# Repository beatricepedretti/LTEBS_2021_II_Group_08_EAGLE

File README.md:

# LTEBS_2021_II_Group_08_EAGLE

This repository contains the first project for the Electronic Technologies and Biosensors Laboratory course, part of the Biomedical Engineering MSc at Politecnico di Milano.
In this project we designed a schematic, a PCB and two custom components using Autodesk EAGLE. The aim of the work was to design a PCB embedding the PSoC 5LP micro-controller in order to evaluate its performance.

# PCB relevant info

- The PCB manufacturer is MDSrl and therefore we followed the rules explained on their website for PCB design (https://www.mdpcb.com/mddesignrules.html).
the 10mil minimum track width requested in the assignment specifications caused clearance errors at the pins of the MUX, therefore we routed this component using 8mil wires while still using 10mils wires everywhere else. This choice satisfies the manufacturer requirements which report 6mils as the minimum width for traces.
- We positioned the light sensor as far away as possible from the LED in order to avoid luminous interference given by the LED. We also tried to position the light sensor as isolated as possible from "tall" components in order to avoid shadows that could interfere with the sensor's measurements.
- We positioned the temperature sensor as far away as possible from the power supply in order to avoid interference given by possible heating of the power supply.
- For the copper pour we used isolation 8 that is the minimum allowed by the manufacturer
- We put jumpers on side of the board

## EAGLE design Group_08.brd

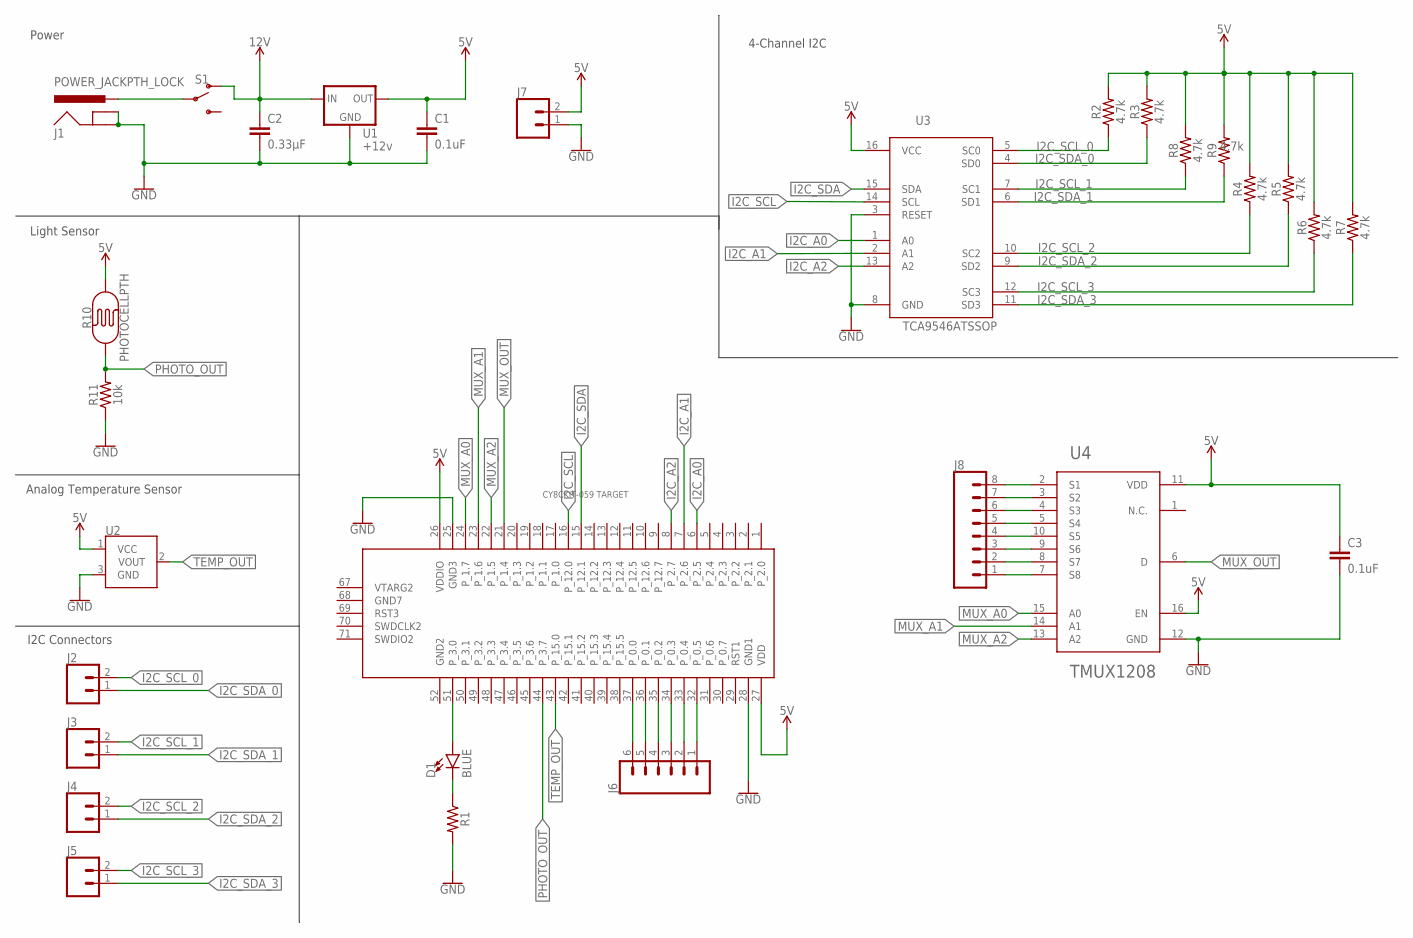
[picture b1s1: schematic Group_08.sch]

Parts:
C1, C3: 0.1uF; CAP-PTH-SMALL-KIT
C2: 0.33µF; 0805
CY8CKIT059-TARGET: CY8CKIT-059_TARGET
D1: BLUE; LED-1206
J1: POWER_JACKPTH_LOCK; POWER_JACK_PTH_LOCK
J2, J3, J4, J5, J7: CONN_02; 1X02
J6: CONN_06LOCK; 1X06_LOCK
J8: CONN_08LOCK; 1X08_LOCK
R1: RESISTORAXIAL-0.3; AXIAL-0.3
R2, R3, R4, R5, R6, R7, R8, R9: 4.7k; 0603
R10: PHOTOCELLPTH; PHOTOCELL
R11: 10k; 0603
S1: SWITCH-SPDT-PTH-11.6X4.0MM; SWITCH_SPDT_PTH_11.6X4.0MM
U1: +12v; TO-252
U2: TMP36GT9; TO-92
U3: TCA9546ATSSOP; TSSOP16
U4: TMUX1208; QFN16

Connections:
5V: C1.1, C3.1, CY8CKIT059-TARGET.26 (VDDIO), CY8CKIT059-TARGET.27 (VDD), J7.2, R2.2, R3.2, R4.2, R5.2, R6.2, R7.2, R8.2, R9.2, R10.2, U1.2 (OUT), U2.1 (VCC), U3.16 (VCC), U4.11 (VDD), U4.16 (EN)
12V: C2.1, S1.1 (O), U1.1 (IN)
GND: C1.2, C2.2, C3.2, CY8CKIT059-TARGET.25 (GND3), CY8CKIT059-TARGET.28 (GND1), J1.GND, J1.GNDBREAK, J7.1, R1.P$2 (2), R11.1, U1.3 (GND), U2.3 (GND), U3.3 (RESET), U3.8 (GND), U4.12 (GND)
I2C_A0: CY8CKIT059-TARGET.6 (P_2.5), U3.1 (A0)
I2C_A1: CY8CKIT059-TARGET.7 (P_2.6), U3.2 (A1)
I2C_A2: CY8CKIT059-TARGET.8 (P_2.7), U3.13 (A2)
I2C_SCL: CY8CKIT059-TARGET.16 (P_12.0), U3.14 (SCL)
I2C_SCL_0: J2.2, R2.1, U3.5 (SC0)
I2C_SCL_1: J3.2, R8.1, U3.7 (SC1)
I2C_SCL_2: J4.2, R4.1, U3.10 (SC2)
I2C_SCL_3: J5.2, R6.1, U3.12 (SC3)
I2C_SDA: CY8CKIT059-TARGET.15 (P_12.1), U3.15 (SDA)
I2C_SDA_0: J2.1, R3.1, U3.4 (SD0)
I2C_SDA_1: J3.1, R9.1, U3.6 (SD1)
I2C_SDA_2: J4.1, R5.1, U3.9 (SD2)
I2C_SDA_3: J5.1, R7.1, U3.11 (SD3)
MUX_A0: CY8CKIT059-TARGET.24 (P_1.7), U4.15 (A0)
MUX_A1: CY8CKIT059-TARGET.23 (P_1.6), U4.14 (A1)
MUX_A2: CY8CKIT059-TARGET.22 (P_1.5), U4.13 (A2)
MUX_OUT: CY8CKIT059-TARGET.21 (P_1.4), U4.6 (D)
unnamed: J1.PWR, S1.2
unnamed: J8.1, U4.7 (S8)
unnamed: J8.2, U4.8 (S7)
unnamed: J8.3, U4.9 (S6)
unnamed: J8.4, U4.10 (S5)
unnamed: J8.5, U4.5 (S4)
unnamed: J8.6, U4.4 (S3)
unnamed: J8.7, U4.3 (S2)
unnamed: J8.8, U4.2 (S1)
unnamed: CY8CKIT059-TARGET.37 (P_0.0), J6.6
unnamed: CY8CKIT059-TARGET.32 (P_0.5), J6.1
unnamed: CY8CKIT059-TARGET.33 (P_0.4), J6.2
unnamed: CY8CKIT059-TARGET.34 (P_0.3), J6.3
unnamed: CY8CKIT059-TARGET.35 (P_0.2), J6.4
unnamed: CY8CKIT059-TARGET.36 (P_0.1), J6.5
unnamed: D1.C, R1.P$1 (1)
unnamed: CY8CKIT059-TARGET.51 (P_3.0), D1.A
PHOTO_OUT: CY8CKIT059-TARGET.44 (P_3.7), R10.1, R11.2
TEMP_OUT: CY8CKIT059-TARGET.43 (P_15.0), U2.2 (VOUT)

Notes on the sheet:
Light Sensor
Analog Temperature Sensor
Power
4-Channel I2C
I2C Connectors

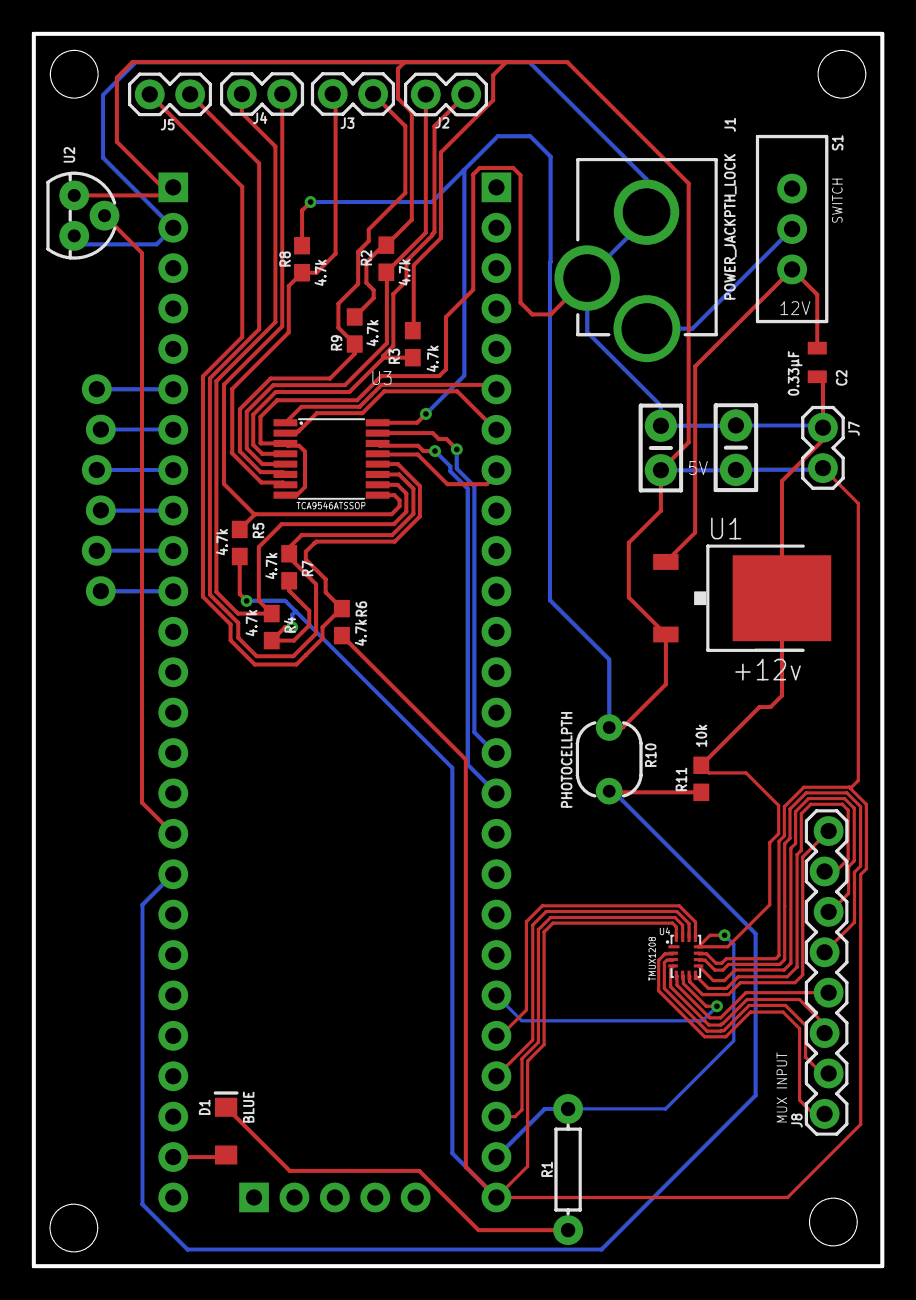
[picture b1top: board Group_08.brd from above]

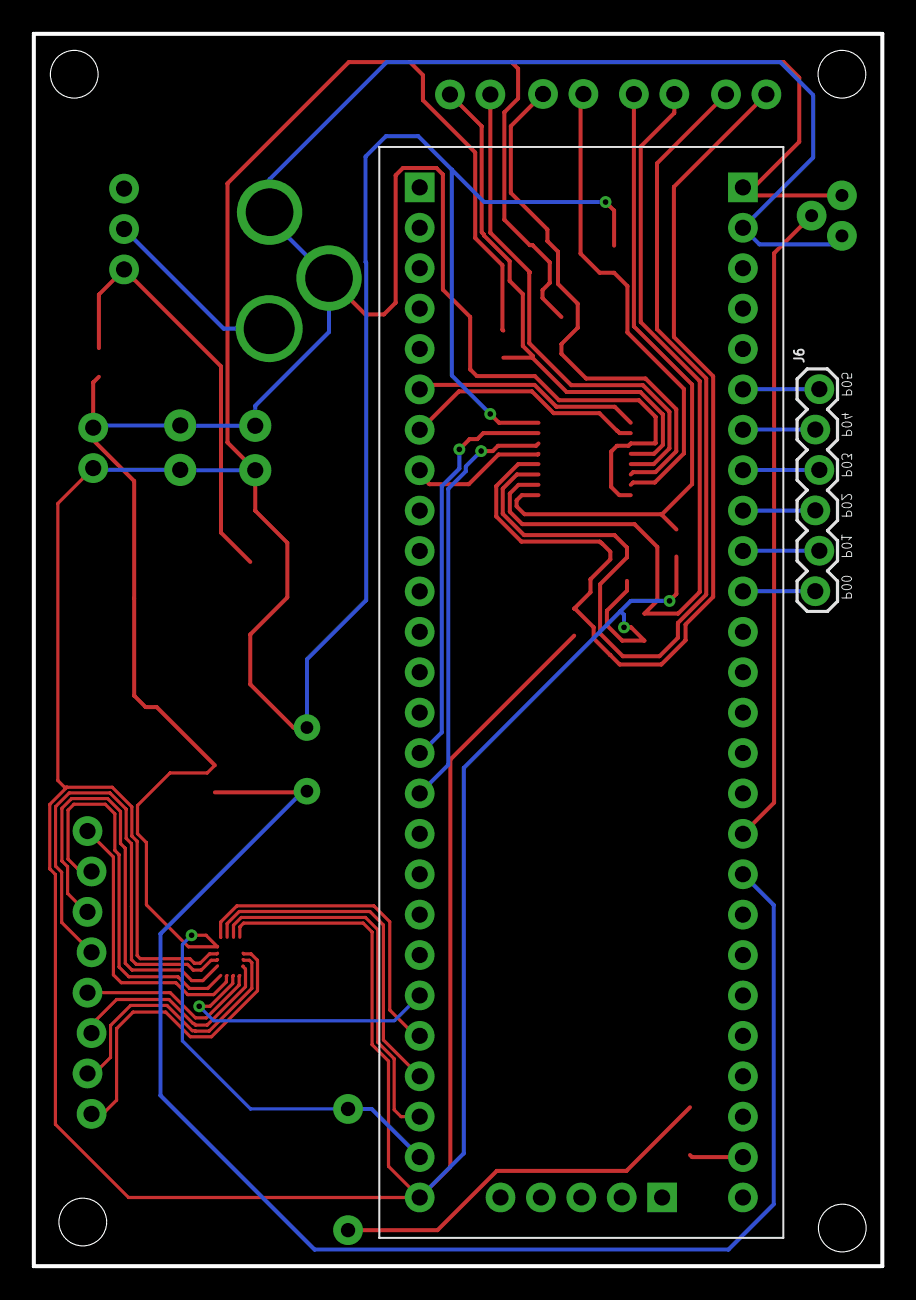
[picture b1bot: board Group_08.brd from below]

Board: 2 copper layers, 53.3 x 77.5 mm, 29 parts (2 on the bottom side), 39 nets.

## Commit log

2021-03-19 Removed .pdf files
2021-03-19 Added TMUX1208 device to general library ('Group_08_Library.lbr') for the moment. Saved the device in an additional library ('TMUX1208.lbr') for safety.
2021-03-19 Modified TMUX1208 symbol in both libraries
2021-03-19 Modified symbol to match reference schematics
2021-03-20 = Added TCA9546A
2021-03-20 Deleted backup file
2021-03-20 Adjusted TMUX1208 footprint
2021-03-22 Modified description headline of device
2021-03-22 First schematic prototype. Need to adjust nets
2021-03-24 completed wiring
2021-03-24 no changes, used correct username
2021-03-24 Fixed TCA9546A layers
2021-03-24 Fixed wiring and did small aesthetic adjustments to library symbols
2021-03-25 board with almoost all wiring done
2021-03-25 real board file
2021-03-25 Alternative version; 0 errors. Already done all wiring and copper pour. Need to add silkscreen and it's possible to reduce board size.
2021-03-25 Mia versione della board
2021-03-25 added silkscreen
2021-03-25 Optimized board, added silkscreen. 0 errors after performing DCR.
2021-03-25 Deleted original prototypes and updated file names
2021-03-25 Deleted old files
2021-03-25 Added standard .gitignore for EAGLE files, from SparkFun library repo
2021-03-26 minor adjustments at wire positioning and silkscreen
2021-03-26 edited track width comments for clarity
2021-03-26 Updated schematics connections
2021-03-26 Trying to make a smaller board
2021-03-26 completed routing of smaller board
2021-03-26 Adjustments to board file
2021-03-26 Added stuff to silkscreen
2021-03-26 Deleted redundant files
2021-03-26 Renamed files correctly
2021-03-26 Final version
2021-03-26 Modified design rules

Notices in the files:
parts and their libraries:
SparkFun-Capacitors: Licensing: Creative Commons ShareAlike 4.0 International - https://creativecommons.org/licenses/by-sa/4.0
